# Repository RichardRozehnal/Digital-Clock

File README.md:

# Digital Clock

Jednoduché digitální hodiny ze čtyř 7mi segmentových displejů.

#### Funkce tlačítek (z boku):
1. tlačítko - zapne nastavování hodin
2. tlačítko - přepíná hodiny nebo minuty nahoru
3. tlačítko - přepíná hodiny nebo minuty dolů

## Další fotky

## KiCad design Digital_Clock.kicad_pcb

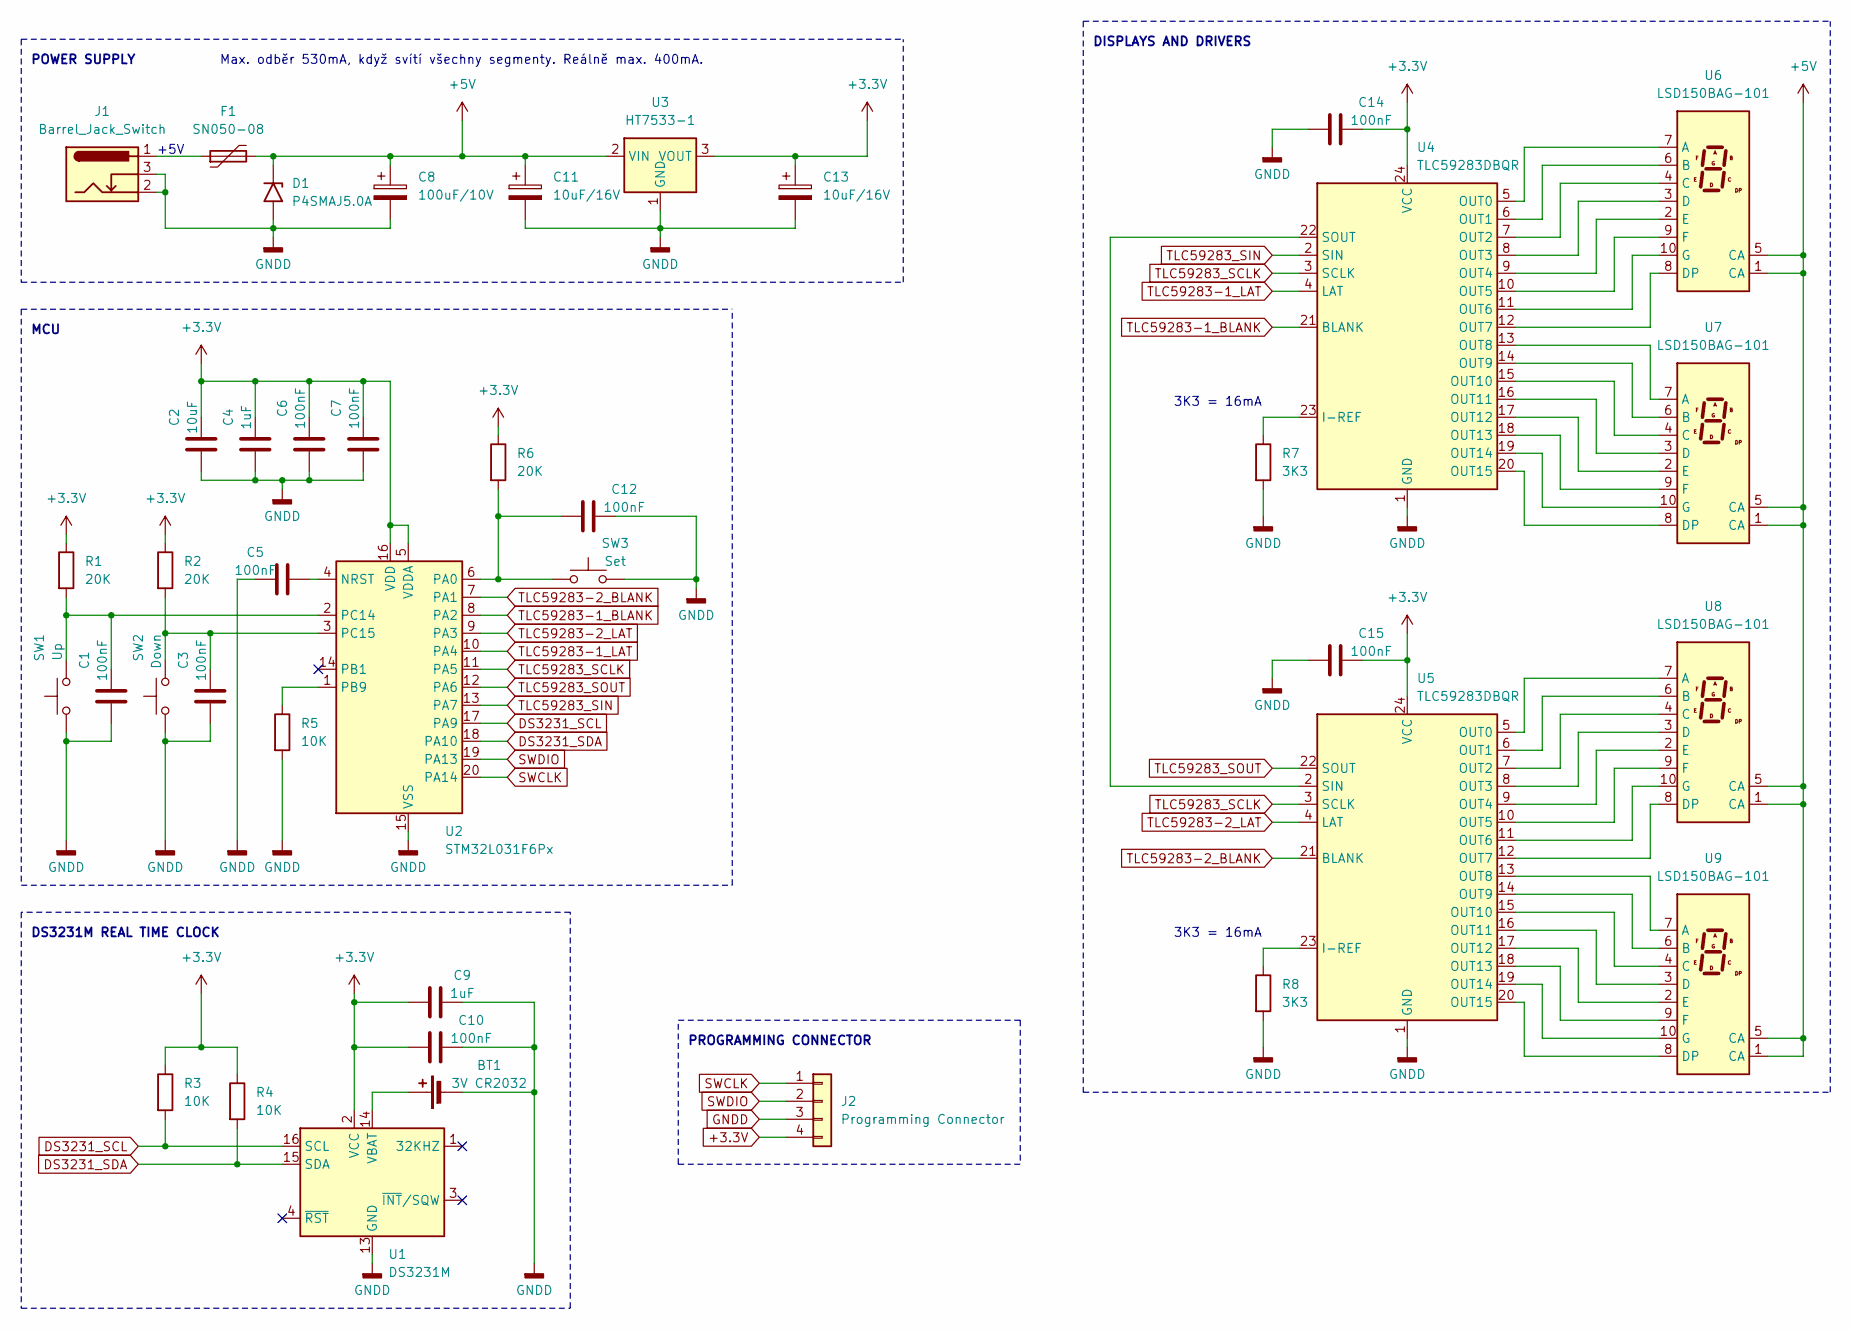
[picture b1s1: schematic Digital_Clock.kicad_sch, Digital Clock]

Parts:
BT1: 3V CR2032; BatteryHolder_ComfortableElectronic_CH273-2450_1x2450
C1, C3, C5, C6, C7, C10, C12, C14, C15: 100nF; C_1206_3216Metric
C2: 10uF; C_1206_3216Metric
C4, C9: 1uF; C_1206_3216Metric
C8: 100uF/10V; CP_Radial_D5.0mm_P2.00mm
C11, C13: 10uF/16V; CP_EIA-3216-18_Kemet-A
D1: P4SMAJ5.0A; D_SMA
F1: SN050-08; Fuse_1206_3216Metric
J1: Barrel_Jack_Switch; BarrelJack_Horizontal
J2: Programming Connector; PinHeader_1x04_P2.54mm_Vertical
R1, R2, R6: 20K; R_1206_3216Metric
R3, R4, R5: 10K; R_1206_3216Metric
R7, R8: 3K3; R_1206_3216Metric
SW1: Up; SW_PUSH_6mm_H13mm
SW2: Down; SW_PUSH_6mm_H13mm
SW3: Set; SW_PUSH_6mm_H13mm
U1: DS3231M; SOIC-16W_7.5x10.3mm_P1.27mm
U2: STM32L031F6Px; TSSOP-20_4.4x6.5mm_P0.65mm
U3: HT7533-1; SOT-89-3
U4, U5: TLC59283DBQR; QSOP-24_3.9x8.7mm_P0.635mm
U6, U7, U8, U9: LSD150BAG-101

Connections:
+3.3V: C2.2, C4.2, C6.2, C7.2, C9.1, C10.1, C13.1, C14.2, C15.2, J2.4, R1.1, R2.1, R3.1, R4.1, R6.1, U1.2 (VCC), U2.5 (VDDA), U2.16 (VDD), U3.3 (VOUT), U4.24 (VCC), U5.24 (VCC)
+5V: C8.1, C11.1, D1.1 (A1), F1.2, U3.2 (VIN), U6.1 (CA), U6.5 (CA), U7.1 (CA), U7.5 (CA), U8.1 (CA), U8.5 (CA), U9.1 (CA), U9.5 (CA)
DS3231_SCL: R3.2, U1.16 (SCL), U2.17 (PA9)
DS3231_SDA: R4.2, U1.15 (SDA), U2.18 (PA10)
GNDD: BT1.2 (-), C1.1, C2.1, C3.1, C4.1, C5.1, C6.1, C7.1, C8.2, C9.2, C10.2, C11.2, C12.2, C13.2, C14.1, C15.1, D1.2 (A2), J1.2, J1.3, J2.3, R5.2, R7.2, R8.2, SW1.1, SW2.1, SW3.2, U1.5 (GND), U1.6 (GND), U1.7 (GND), U1.8 (GND), U1.9 (GND), U1.10 (GND), U1.11 (GND), U1.12 (GND), U1.13 (GND), U2.15 (VSS), U3.1 (GND), U4.1 (GND), U5.1 (GND)
unnamed: BT1.1 (+), U1.14 (VBAT)
unnamed: F1.1, J1.1
unnamed: C5.2, U2.4 (NRST)
unnamed: C12.1, R6.2, SW3.1, U2.6 (PA0)
unnamed: R5.1, U2.1 (PB9)
unnamed: C1.2, R1.2, SW1.2, U2.2 (PC14)
unnamed: C3.2, R2.2, SW2.2, U2.3 (PC15)
unnamed: R7.1, U4.23 (I-REF)
unnamed: U4.5 (OUT0), U6.7 (A)
unnamed: U4.6 (OUT1), U6.6 (B)
unnamed: U4.7 (OUT2), U6.4 (C)
unnamed: U4.8 (OUT3), U6.3 (D)
unnamed: U4.9 (OUT4), U6.2 (E)
unnamed: U4.10 (OUT5), U6.9 (F)
unnamed: U4.11 (OUT6), U6.10 (G)
unnamed: U4.12 (OUT7), U6.8 (DP)
unnamed: U4.13 (OUT8), U7.7 (A)
unnamed: U4.14 (OUT9), U7.6 (B)
unnamed: U4.15 (OUT10), U7.4 (C)
unnamed: U4.16 (OUT11), U7.3 (D)
unnamed: U4.17 (OUT12), U7.2 (E)
unnamed: U4.18 (OUT13), U7.9 (F)
unnamed: U4.19 (OUT14), U7.10 (G)
unnamed: U4.20 (OUT15), U7.8 (DP)
unnamed: U4.22 (SOUT), U5.2 (SIN)
unnamed: R8.1, U5.23 (I-REF)
unnamed: U5.5 (OUT0), U8.7 (A)
unnamed: U5.6 (OUT1), U8.6 (B)
unnamed: U5.7 (OUT2), U8.4 (C)
unnamed: U5.8 (OUT3), U8.3 (D)
unnamed: U5.9 (OUT4), U8.2 (E)
unnamed: U5.10 (OUT5), U8.9 (F)
unnamed: U5.11 (OUT6), U8.10 (G)
unnamed: U5.12 (OUT7), U8.8 (DP)
unnamed: U5.13 (OUT8), U9.7 (A)
unnamed: U5.14 (OUT9), U9.6 (B)
unnamed: U5.15 (OUT10), U9.4 (C)
unnamed: U5.16 (OUT11), U9.3 (D)
unnamed: U5.17 (OUT12), U9.2 (E)
unnamed: U5.18 (OUT13), U9.9 (F)
unnamed: U5.19 (OUT14), U9.10 (G)
unnamed: U5.20 (OUT15), U9.8 (DP)
SWCLK: J2.1, U2.20 (PA14)
SWDIO: J2.2, U2.19 (PA13)
TLC59283-1_BLANK: U2.8 (PA2), U4.21 (BLANK)
TLC59283-1_LAT: U2.10 (PA4), U4.4 (LAT)
TLC59283-2_BLANK: U2.7 (PA1), U5.21 (BLANK)
TLC59283-2_LAT: U2.9 (PA3), U5.4 (LAT)
TLC59283_SCLK: U2.11 (PA5), U4.3 (SCLK), U5.3 (SCLK)
TLC59283_SIN: U2.13 (PA7), U4.2 (SIN)
TLC59283_SOUT: U2.12 (PA6), U5.22 (SOUT)

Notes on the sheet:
3K3 = 16mA
POWER SUPPLY
DS3231M REAL TIME CLOCK
MCU
+5V
Max. odběr 530mA, když svítí všechny segmenty. Reálně max. 400mA.
DISPLAYS AND DRIVERS
PROGRAMMING CONNECTOR

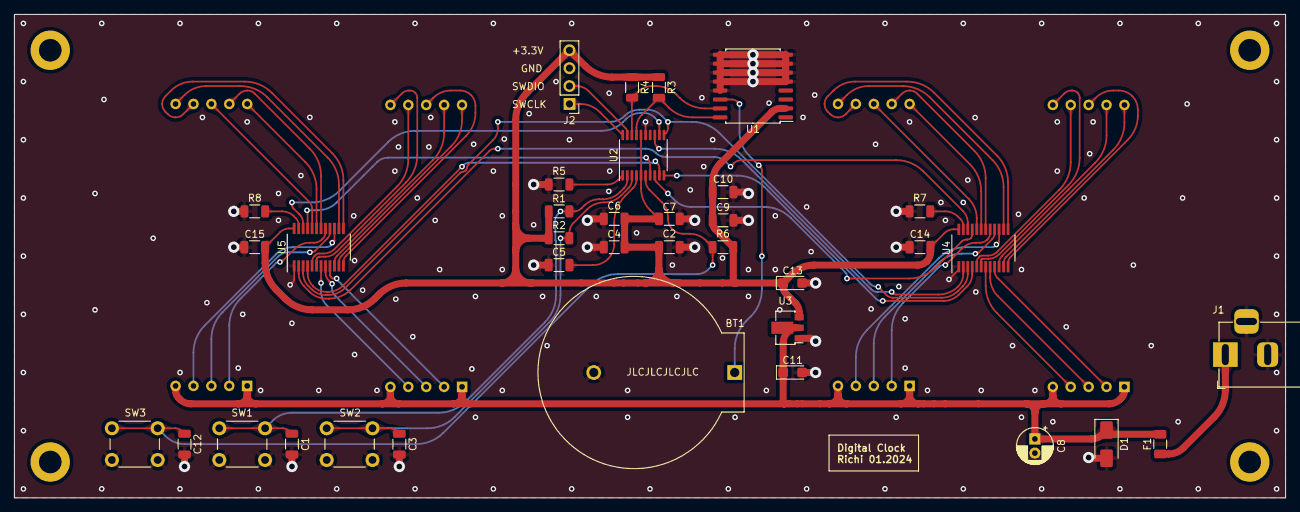
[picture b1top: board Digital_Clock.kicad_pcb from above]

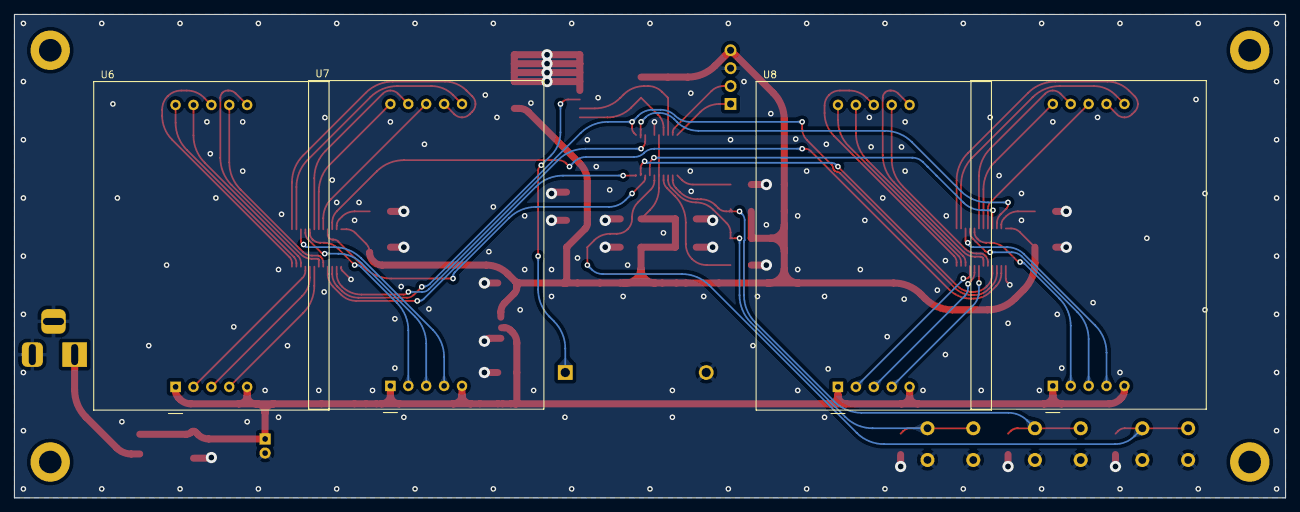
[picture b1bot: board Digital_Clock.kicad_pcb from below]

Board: 2 copper layers, 180.3 x 68.6 mm, 40 parts (4 on the bottom side), 56 nets.

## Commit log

2024-03-10 Create 1
2024-03-10 Create a
